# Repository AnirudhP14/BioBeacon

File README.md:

# BioBeacon

ESP32 based stigmergic swarm built on esp-now.

# HiveMind - BioBeacon's swarm monitoring

# Custom PCB for BioBeacob

white a01
red a02

white b01
red b02

Left motor encoder C1 → ENCA_C1 (GPIO2). green  D2
Left motor encoder C2 → ENCA_C2 (GPIO3).  yellow D3
Right motor encoder C1 → ENCB_C1 (GPIO11) green D11
Right motor encoder C2 → ENCB_C2 (GPIO12) yellow D12

Enc VCC - black 
Enc Gnd - purple

D0	GPIO44
D1	GPIO43
D2	GPIO5
D3	GPIO6
D4	GPIO7
D5	GPIO8
D6	GPIO9
D7	GPIO10
D8	GPIO17
D9	GPIO18
D10	GPIO21
D11	GPIO38
D12	GPIO47
D13	GPIO48
A0	GPIO1
A1	GPIO2
A2	GPIO3
A3	GPIO4
A4	GPIO11
A5	GPIO12
A6	GPIO13
A7	GPIO14
BOOT0	GPIO46
BOOT1	GPIO0

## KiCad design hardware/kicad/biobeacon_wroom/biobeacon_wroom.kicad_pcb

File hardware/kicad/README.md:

# Kicad pcb files

This folder contains Ki-cad PCB files for
- BioBeacon ESP32 Wroom board
- BioBeacon sensor board - daughter board
- TB6612FNG motor board 

Additional ESP32 boards to be added to support additional ESP32 variants.
Separate TB6612FNG daughter board could provide more flexibility.

# Custom PCB for BioBeacob

# Schematic for BioBeacon Motherboard 

# Sensorboard daugther board 

# Motor driver daugther board

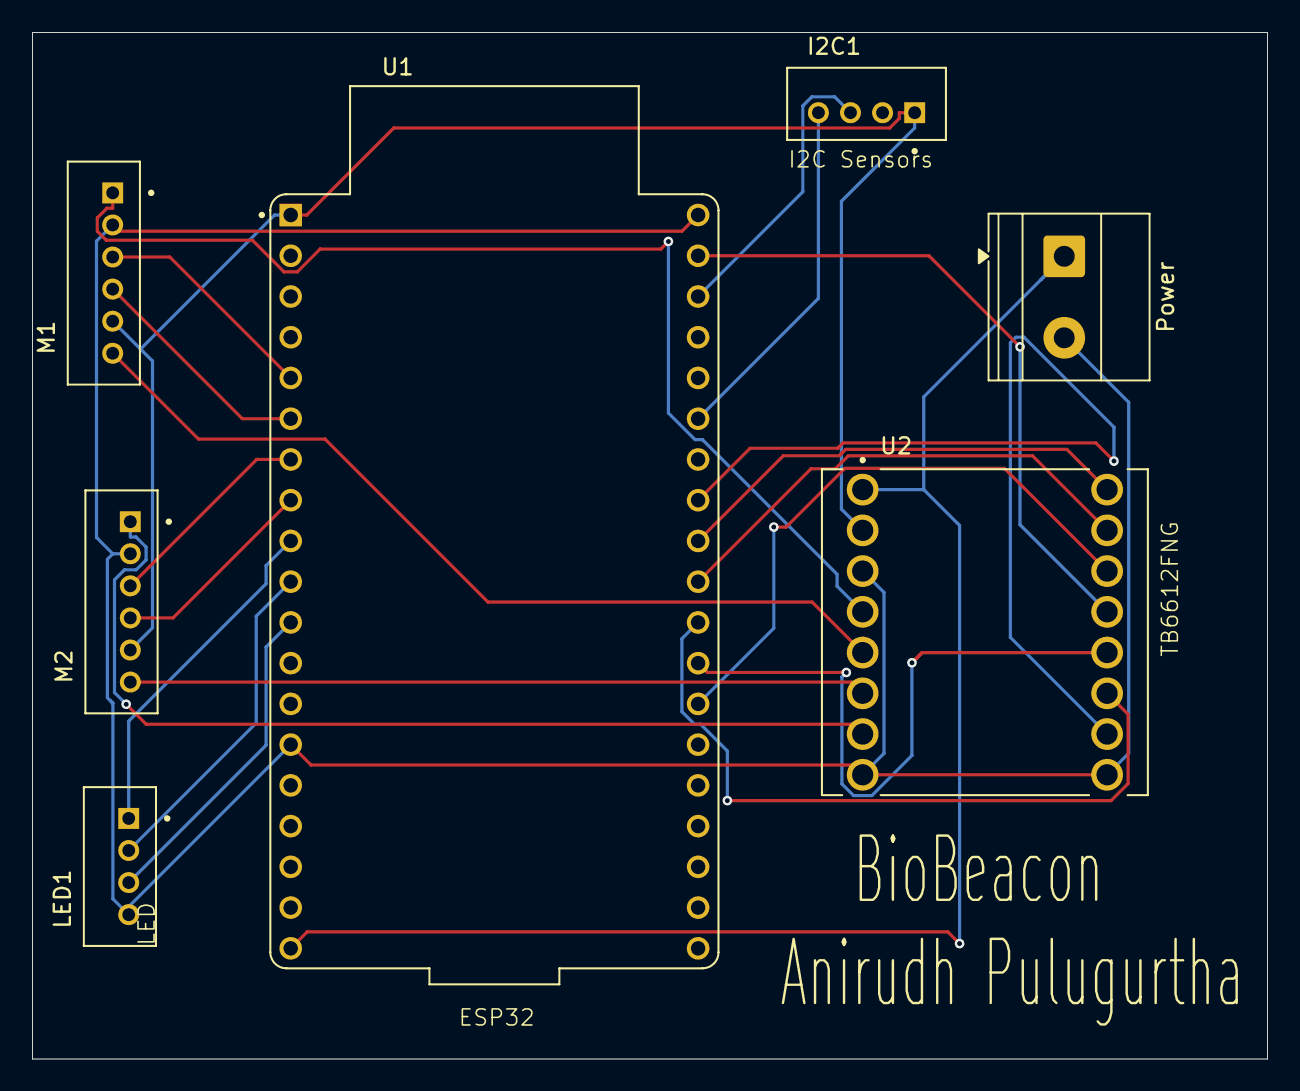
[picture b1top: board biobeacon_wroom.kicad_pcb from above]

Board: 2 copper layers, 77.0 x 64.0 mm, 7 parts (0 on the bottom side), 23 nets.

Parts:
I2C1: Conn_01x04; JST_B4B-PH-K
LED1: Conn_01x04; JST_B4B-PH-K
M1, M2: Conn_01x06; JST_B6B-PH-K
Power: Screw_Terminal_01x02; TerminalBlock_Phoenix_MKDS-1,5-2-5.08_1x02_P5.08mm_Horizont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
U1: ESP32-DEVKITC-32E; MODULE_ESP32-DEVKITC-32E
U2: ROB-14450; MODULE_ROB-14450

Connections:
GND: LED1.4, M1.2, M2.2, Power.2, U1.J2_14 (GND_J2_14), U1.J3_1 (GND_J3_1), U2.3 (GND), U2.8 (GND), U2.9 (GND)
unnamed: I2C1.1, M1.5, M2.5, U1.J2_1 (3V3), U2.2 (VCC)
unnamed: I2C1.3, U1.J3_3 (IO22)
unnamed: I2C1.4, U1.J3_6 (IO21)
unnamed: Power.1, U1.J2_19 (EXT_5V), U2.1 (VM)
unnamed: LED1.1, U1.J2_9 (IO25)
unnamed: LED1.2, U1.J2_10 (IO26)
unnamed: LED1.3, U1.J2_11 (IO27)
unnamed: M1.1, U2.4 (A01)
unnamed: M1.3, U1.J2_5 (IO34)
unnamed: M1.4, U1.J2_6 (IO35)
unnamed: M1.6, U2.5 (A02)
unnamed: M2.1, U2.7 (B01)
unnamed: M2.3, U1.J2_7 (IO32)
unnamed: M2.4, U1.J2_8 (IO33)
unnamed: M2.6, U2.6 (B02)
unnamed: U1.J3_13 (IO4), U2.14 (AI1)
unnamed: U1.J3_10 (IO5), U2.15 (AI2)
unnamed: U1.J3_12 (IO16), U2.12 (BI1)
unnamed: U1.J3_11 (IO17), U2.11 (BI2)
unnamed: U1.J3_9 (IO18), U2.16 (PWMA)
unnamed: U1.J3_8 (IO19), U2.10 (PWMB)
unnamed: U1.J3_2 (IO23), U2.13 (STBY)

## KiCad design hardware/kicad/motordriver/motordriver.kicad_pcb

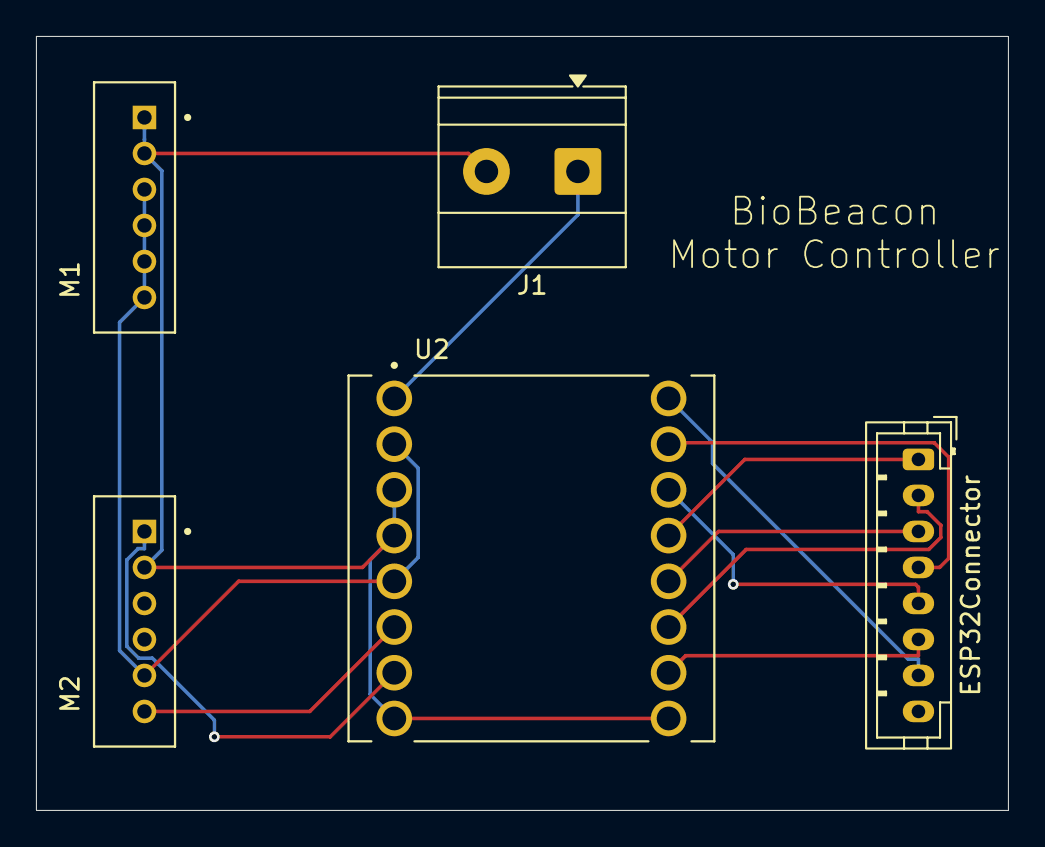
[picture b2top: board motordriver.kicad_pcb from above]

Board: 2 copper layers, 54.0 x 43.0 mm, 5 parts (0 on the bottom side), 12 nets.

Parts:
ESP32Connector: Conn_01x08_Socket; JST_PH_B8B-PH-K_1x08_P2.00mm_Vertical
J1: Screw_Terminal_01x02; TerminalBlock_Phoenix_MKDS-1,5-2-5.08_1x02_P5.08mm_Horizont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
M1, M2: Conn_01x06; JST_B6B-PH-K
U2: ROB-14450; MODULE_ROB-14450

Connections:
GND: J1.2, M1.1, M1.2, M2.2, U2.3 (GND), U2.4 (A01), U2.8 (GND), U2.9 (GND)
unnamed: J1.1, U2.1 (VM)
unnamed: ESP32Connector.1, U2.13 (STBY)
unnamed: ESP32Connector.2, U2.11 (BI2)
unnamed: ESP32Connector.3, U2.12 (BI1)
unnamed: ESP32Connector.4, U2.15 (AI2)
unnamed: ESP32Connector.5, U2.14 (AI1)
unnamed: ESP32Connector.6, U2.10 (PWMB)
unnamed: ESP32Connector.7, U2.16 (PWMA)
unnamed: M1.3, M1.4, M1.5, M1.6, M2.5, U2.2 (VCC), U2.5 (A02)
unnamed: M2.1, U2.7 (B01)
unnamed: M2.6, U2.6 (B02)

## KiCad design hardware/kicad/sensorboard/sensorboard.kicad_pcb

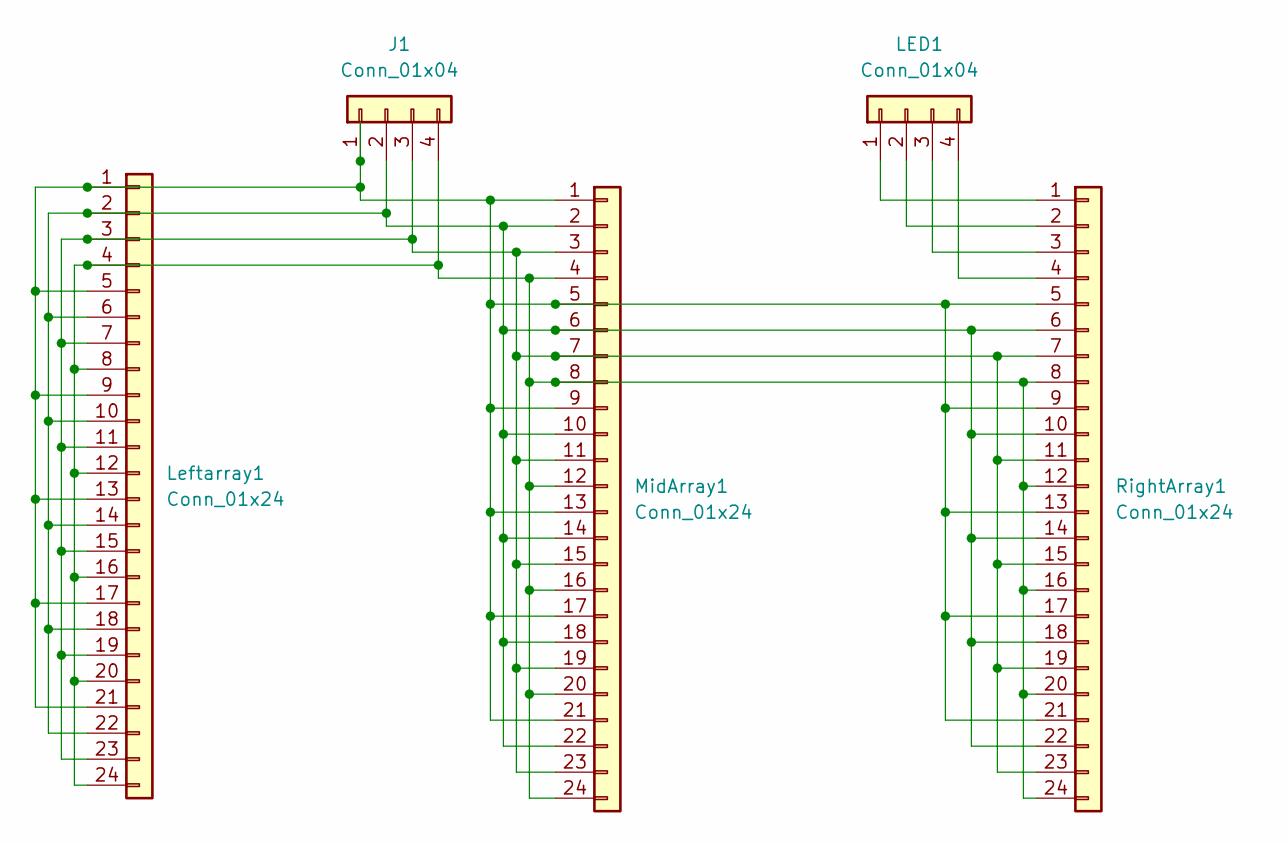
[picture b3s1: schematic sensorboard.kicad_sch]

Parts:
J1: Conn_01x04; JST_PH_B4B-PH-K_1x04_P2.00mm_Vertical
LED1: Conn_01x04; JST_PH_B4B-PH-K_1x04_P2.00mm_Vertical
Leftarray1: Conn_01x24; PinSocket_1x24_P1.00mm_Vertical
MidArray1: Conn_01x24; PinSocket_1x24_P1.00mm_Vertical
RightArray1: Conn_01x24; PinSocket_1x24_P1.00mm_Vertical

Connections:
unnamed: J1.1, Leftarray1.1, Leftarray1.5, Leftarray1.9, Leftarray1.13, Leftarray1.17, Leftarray1.21, MidArray1.1, MidArray1.5, MidArray1.9, MidArray1.13, MidArray1.17, MidArray1.21, RightArray1.5, RightArray1.9, RightArray1.13, RightArray1.17, RightArray1.21
unnamed: J1.2, Leftarray1.2, Leftarray1.6, Leftarray1.10, Leftarray1.14, Leftarray1.18, Leftarray1.22, MidArray1.2, MidArray1.6, MidArray1.10, MidArray1.14, MidArray1.18, MidArray1.22, RightArray1.6, RightArray1.10, RightArray1.14, RightArray1.18, RightArray1.22
unnamed: J1.3, Leftarray1.3, Leftarray1.7, Leftarray1.11, Leftarray1.15, Leftarray1.19, Leftarray1.23, MidArray1.3, MidArray1.7, MidArray1.11, MidArray1.15, MidArray1.19, MidArray1.23, RightArray1.7, RightArray1.11, RightArray1.15, RightArray1.19, RightArray1.23
unnamed: J1.4, Leftarray1.4, Leftarray1.8, Leftarray1.12, Leftarray1.16, Leftarray1.20, Leftarray1.24, MidArray1.4, MidArray1.8, MidArray1.12, MidArray1.16, MidArray1.20, MidArray1.24, RightArray1.8, RightArray1.12, RightArray1.16, RightArray1.20, RightArray1.24
unnamed: LED1.1, RightArray1.1
unnamed: LED1.2, RightArray1.2
unnamed: LED1.3, RightArray1.3
unnamed: LED1.4, RightArray1.4

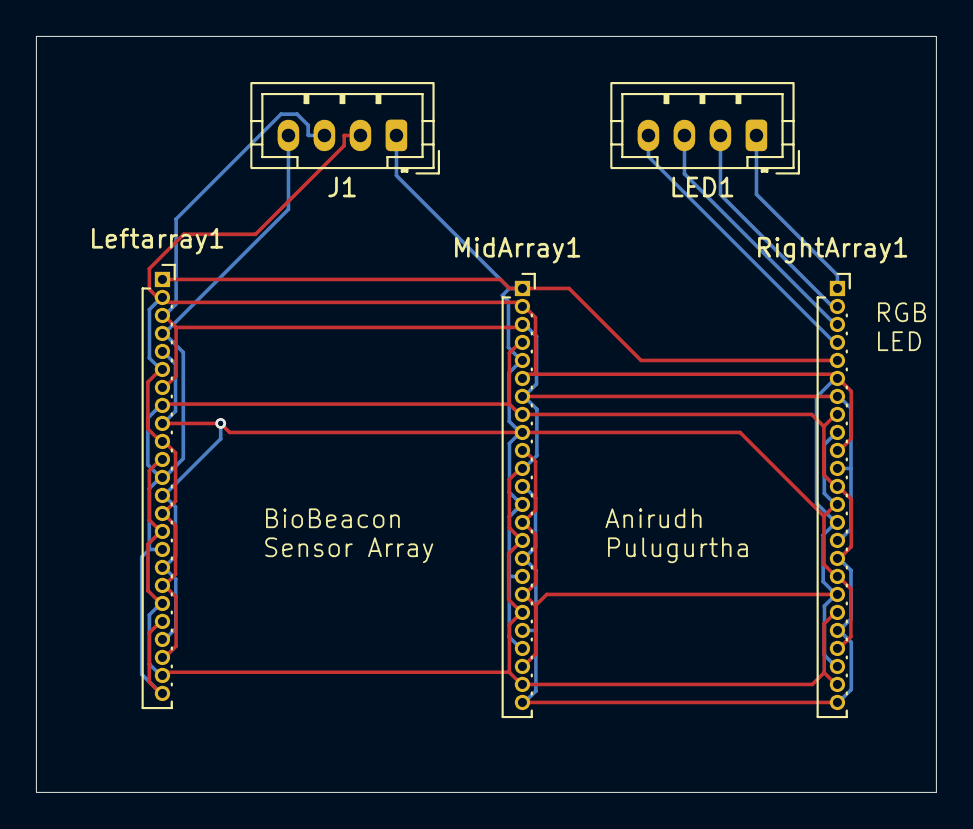
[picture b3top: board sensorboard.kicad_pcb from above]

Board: 2 copper layers, 50.0 x 42.0 mm, 5 parts (0 on the bottom side), 8 nets.

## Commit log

2026-01-15 Add initial README.md for src folder
2026-01-15 initial commit.
2026-01-15 cleanup
2026-01-15 Update README with project description
    Add project description for BioBeacon.
2026-01-16 Fix image link syntax in README.md
2026-02-22 kicad schematics and pcb design files
2026-02-22 biobeacon pcb render
2026-02-24 3d prints of robot and survival tools
2026-02-24 software folder
2026-04-09 hivemind
2026-04-09 fix image hivemind
